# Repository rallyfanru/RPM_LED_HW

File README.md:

# RPM_LED_HW
Аппаратная часть проекта https://github.com/rallyfanru/RPM_LED  
Проект сделан в Kicad 5  
Требует исправления, список ошибок в changelog.txt

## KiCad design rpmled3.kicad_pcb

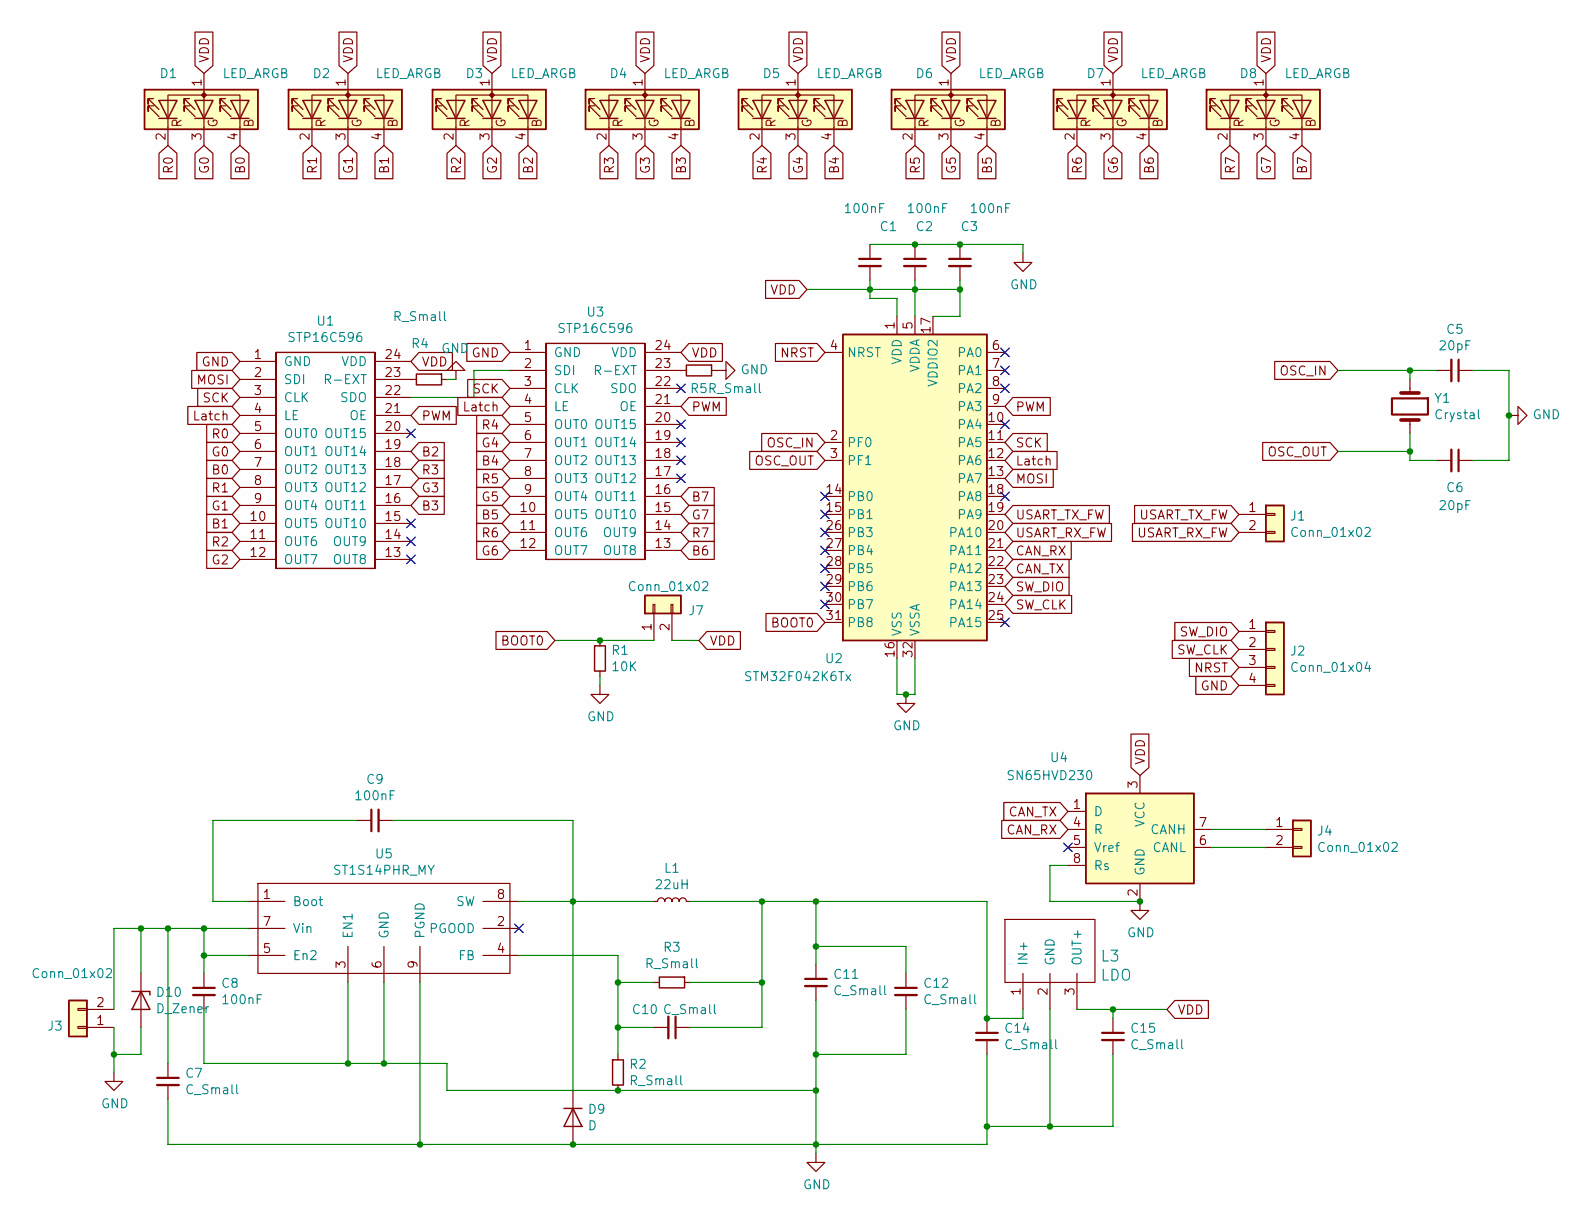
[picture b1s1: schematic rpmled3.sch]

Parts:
C1, C2, C3, C8, C9: 100nF; C_0805_2012Metric_Pad1.15x1.40mm_HandSolder
C5, C6: 20pF; C_0805_2012Metric_Pad1.15x1.40mm_HandSolder
C7, C14, C15: C_Small; C_1206_3216Metric_Pad1.42x1.75mm_HandSolder
C10: C_Small; C_0805_2012Metric_Pad1.15x1.40mm_HandSolder
C11, C12: C_Small; CP_EIA-7343-31_Kemet-D_Pad2.25x2.55mm_HandSolder
D1, D2, D3, D4, D5, D6, D7, D8: LED_ARGB; RGB_LEB_InLine
D9: D; D_SMB_Handsoldering
D10: D_Zener; D_DO-201AD_P12.70mm_Horizontal
J1, J3, J4, J7: Conn_01x02; PinHeader_1x02_P2.54mm_Vertical
J2: Conn_01x04; PinHeader_1x04_P2.54mm_Vertical
L1: 22uH; L_10.4x10.4_H4.8
L3: LDO; TO-252-3_TabPin2
R1: 10K; R_1206_3216Metric_Pad1.42x1.75mm_HandSolder
R2, R3: R_Small; R_0603_1608Metric_Pad1.05x0.95mm_HandSolder
R4, R5: R_Small; R_1206_HandSoldering
U1, U3: STP16C596; SOIC-24W_7.5x15.4mm_P1.27mm
U2: STM32F042K6Tx; LQFP-32_7x7mm_P0.8mm
U4: SN65HVD230; SOIC-8_3.9x4.9mm_P1.27mm
U5: ST1S14PHR_MY; SOIC-8-1EP_3.9x4.9mm_P1.27mm_EP2.35x2.35mm
Y1: Crystal; Crystal_HC49-4H_Vertical

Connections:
B0: D1.4 (BK), U1.7 (OUT2)
B1: D2.4 (BK), U1.10 (OUT5)
B2: D3.4 (BK), U1.19 (OUT14)
B3: D4.4 (BK), U1.16 (OUT11)
B4: D5.4 (BK), U3.7 (OUT2)
B5: D6.4 (BK), U3.10 (OUT5)
B6: D7.4 (BK), U3.13 (OUT8)
B7: D8.4 (BK), U3.16 (OUT11)
BOOT0: J7.1, R1.1, U2.31 (PB8)
CAN_RX: U2.21 (PA11), U4.4 (R)
CAN_TX: U2.22 (PA12), U4.1 (D)
G0: D1.3 (GK), U1.6 (OUT1)
G1: D2.3 (GK), U1.9 (OUT4)
G2: D3.3 (GK), U1.12 (OUT7)
G3: D4.3 (GK), U1.17 (OUT12)
G4: D5.3 (GK), U3.6 (OUT1)
G5: D6.3 (GK), U3.9 (OUT4)
G6: D7.3 (GK), U3.12 (OUT7)
G7: D8.3 (GK), U3.15 (OUT10)
GND: C1.1, C2.1, C3.1, C5.1, C6.1, C7.2, C8.2, C11.2, C12.2, C14.2, C15.2, D9.2 (A), D10.2 (A), J2.4, J3.1, L3.2 (GND), R1.2, R2.2, R4.1, R5.1, U1.1 (GND), U2.16 (VSS), U2.32 (VSSA), U3.1 (GND), U4.2 (GND), U4.8 (Rs), U5.3 (EN1), U5.6 (GND), U5.9 (PGND)
Latch: U1.4 (LE), U2.12 (PA6), U3.4 (LE)
MOSI: U1.2 (SDI), U2.13 (PA7)
NRST: J2.3, U2.4 (NRST)
unnamed: C7.1, C8.1, D10.1 (K), J3.2, U5.5 (En2), U5.7 (Vin)
unnamed: C9.1, U5.1 (Boot)
unnamed: C9.2, D9.1 (K), L1.1, U5.8 (SW)
unnamed: C10.1, C11.1, C12.1, C14.1, L1.2, L3.1 (IN+), R3.1
unnamed: C10.2, R2.1, R3.2, U5.4 (FB)
unnamed: J4.1, U4.7 (CANH)
unnamed: J4.2, U4.6 (CANL)
unnamed: R4.2, U1.23 (R-EXT)
unnamed: R5.2, U3.23 (R-EXT)
unnamed: U1.22 (SDO), U3.2 (SDI)
OSC_IN: C5.2, U2.2 (PF0), Y1.1
OSC_OUT: C6.2, U2.3 (PF1), Y1.2
PWM: U1.21 (OE), U2.9 (PA3), U3.21 (OE)
R0: D1.2 (RK), U1.5 (OUT0)
R1: D2.2 (RK), U1.8 (OUT3)
R2: D3.2 (RK), U1.11 (OUT6)
R3: D4.2 (RK), U1.18 (OUT13)
R4: D5.2 (RK), U3.5 (OUT0)
R5: D6.2 (RK), U3.8 (OUT3)
R6: D7.2 (RK), U3.11 (OUT6)
R7: D8.2 (RK), U3.14 (OUT9)
SCK: U1.3 (CLK), U2.11 (PA5), U3.3 (CLK)
SW_CLK: J2.2, U2.24 (PA14)
SW_DIO: J2.1, U2.23 (PA13)
USART_RX_FW: J1.2, U2.20 (PA10)
USART_TX_FW: J1.1, U2.19 (PA9)
VDD: C1.2, C2.2, C3.2, C15.1, D1.1 (A), D2.1 (A), D3.1 (A), D4.1 (A), D5.1 (A), D6.1 (A), D7.1 (A), D8.1 (A), J7.2, L3.3 (OUT+), U1.24 (VDD), U2.1 (VDD), U2.5 (VDDA), U2.17 (VDDIO2), U3.24 (VDD), U4.3 (VCC)

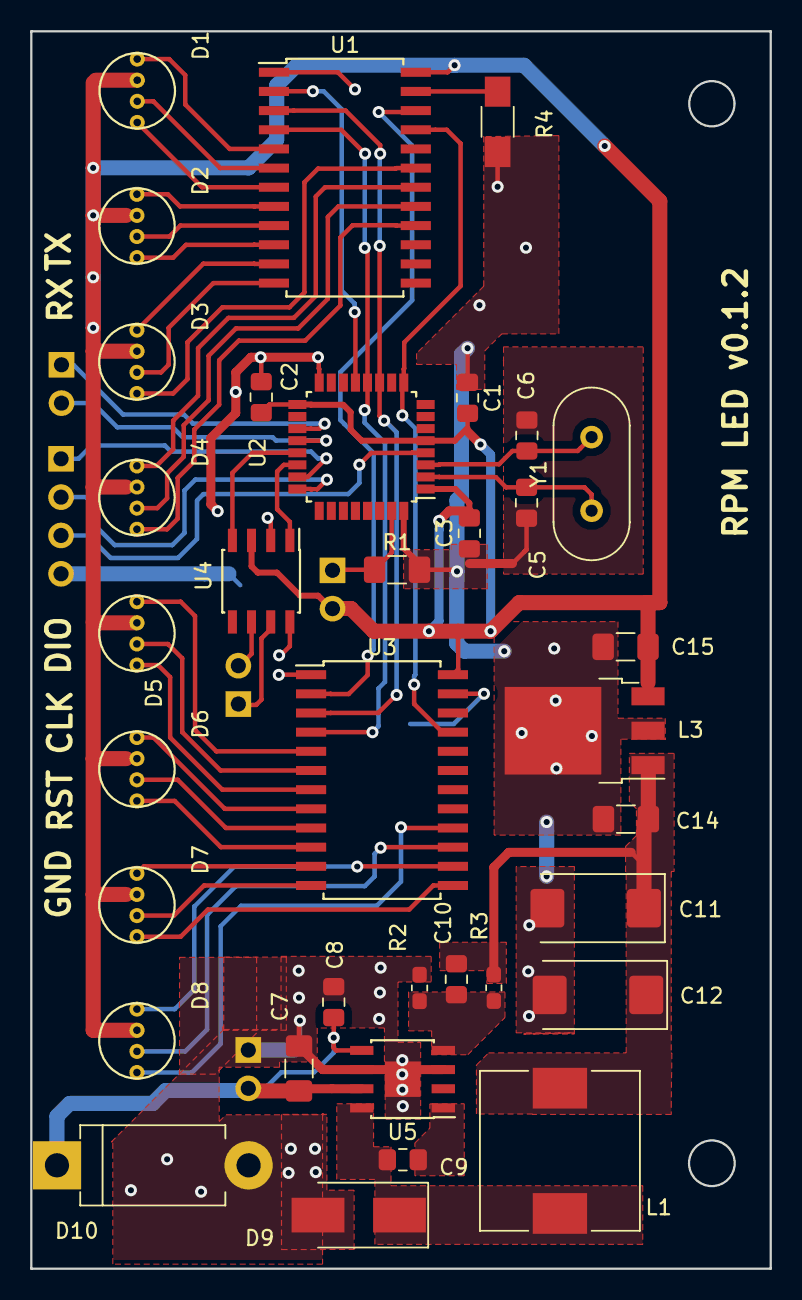
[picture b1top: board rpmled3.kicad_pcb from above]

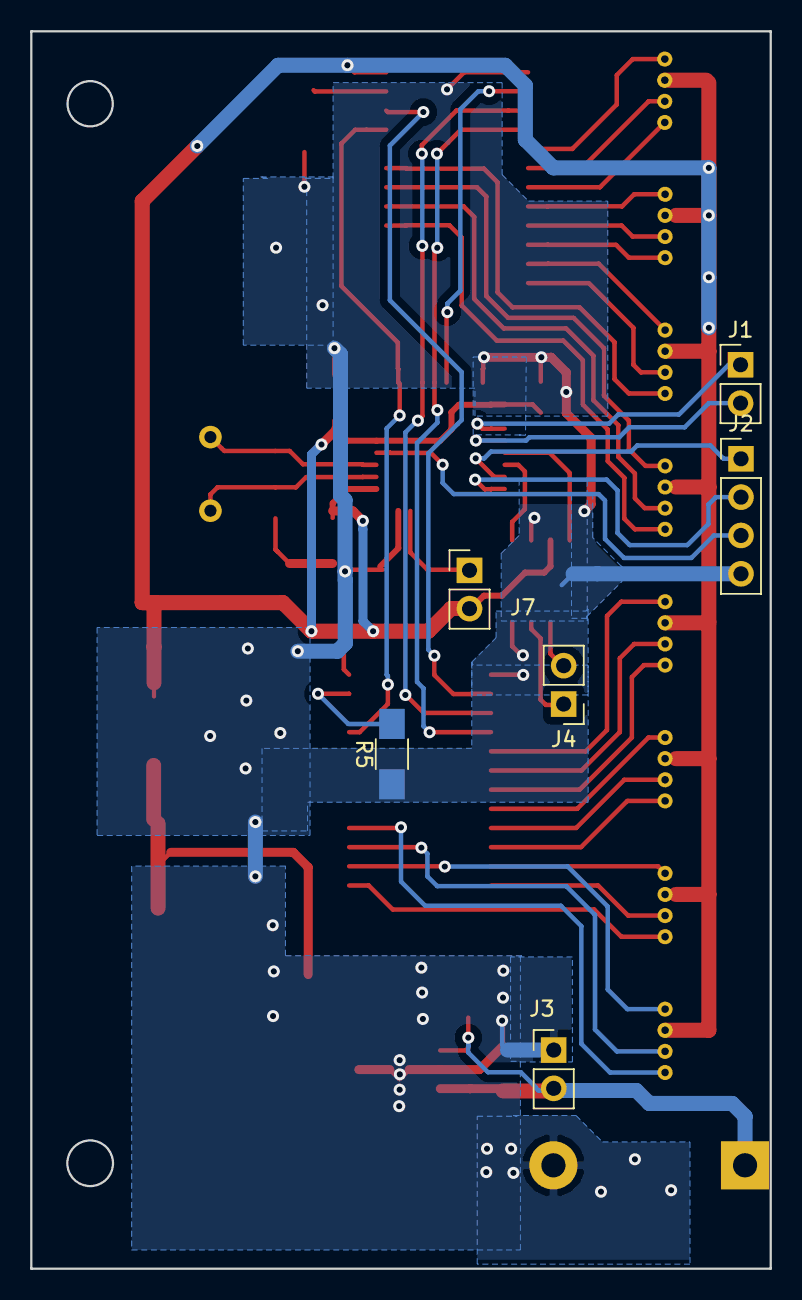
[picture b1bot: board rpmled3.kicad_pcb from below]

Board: 2 copper layers, 49.0 x 82.0 mm, 41 parts (6 on the bottom side), 50 nets.

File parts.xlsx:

|  |  |  |  |  | Итого: | 753.31
 | Обозначение | Элемент | Номинал | Корпус | Код | Ссылка | Цена
 | C11 | конденсатор | 100u | SMD D | 593D107X9010D2TE3 | https://spb.terraelectronica.ru/product/358908 | 24.6
 | C12 | конденсатор | 100u | SMD D | 593D107X9010D2TE3 | https://spb.terraelectronica.ru/product/358908 | 24.6
 | C10 | конденсатор | 1.5p | 0805 | CC0805CRNPO9BN1R5 | https://spb.terraelectronica.ru/product/1107359 | 1.3
 | C5 | конденсатор | 20p | 0805 | CC0805JRNPO9BN200 | https://spb.terraelectronica.ru/product/326950 | 1.3
 | C6 | конденсатор | 20p | 0805 | CC0805JRNPO9BN200 | https://spb.terraelectronica.ru/product/326950 | 1.3
 | C1 | конденсатор | 100n | 0805 | CC0805ZRY5V9BB104 | https://spb.terraelectronica.ru/product/360375 | 2.2
 | C2 | конденсатор | 100n | 0805 | CC0805ZRY5V9BB104 | https://spb.terraelectronica.ru/product/360375 | 2.2
 | C3 | конденсатор | 100n | 0805 | CC0805ZRY5V9BB104 | https://spb.terraelectronica.ru/product/360375 | 2.2
 | C8 | конденсатор | 100n | 0805 | CC0805ZRY5V9BB104 | https://spb.terraelectronica.ru/product/360375 | 2.2
 | C9 | конденсатор | 100n | 0805 | CC0805ZRY5V9BB104 | https://spb.terraelectronica.ru/product/360375 | 2.2
 | C7 | конденсатор | 4.7u | 1206 | CC1206KKX7R9BB475 | https://spb.terraelectronica.ru/product/1320438 | 29.2
 | C14 | конденсатор | 10u | 1206 | CL31B106KPHNNNE | https://spb.terraelectronica.ru/product/1641462 | 6.1
 | C15 | конденсатор | 4.7u | 1206 | GRM31CR71A475KA01L | https://spb.terraelectronica.ru/product/361734 | 8.7
 | D10 | сапрессор | 18B |  | 1.5KE18CA | https://www.chipdip.ru/product/1.5ke18ca | 16
 | D9 | Диод |  | SMB | STPS2L25U | https://spb.terraelectronica.ru/product/236375 | 8.8
 | L1 | индуктивность |  |  | IHLP2525CZER8R2M01 | https://spb.terraelectronica.ru/product/577217 | 36.9
 | L3 | LDO |  |  | NCP5501DT33RKG | https://spb.terraelectronica.ru/product/437019 | 24.8
 | R1 | резистор | 10K | 1206 | CR1206-JW-103ELF | https://spb.terraelectronica.ru/product/1628762 | 0.5
 | R2 | резистор | 60.4K | 0603 | RC0603FR-0760K4L | https://spb.terraelectronica.ru/product/871175 | 0.15
 | R3 | резистор | 187K | 0603 | RC0603FR-07187KL | https://spb.terraelectronica.ru/product/871017 | 0.42
 | R4 | резистор | 1K | 1206 | CR1206-JW-102ELF | https://spb.terraelectronica.ru/product/265324 | 0.62
 | R5 | резистор | 1K | 1206 | CR1206-JW-102ELF | https://spb.terraelectronica.ru/product/265324 | 0.62
 | U1 | STP16CP05 |  |  | STP16CP05MTR | https://spb.terraelectronica.ru/product/274946 | 71.5
 | U2 | STM32F042 |  |  | STM32F042K6T6 | https://spb.terraelectronica.ru/product/1334269 | 160
 | U3 | STP16CP05 |  |  | STP16CP05MTR | https://spb.terraelectronica.ru/product/274946 | 71.5
 | U4 | CAN |  |  | SN65HVD230 | https://spb.terraelectronica.ru/product/176199 | 145
 | U5 | dc-dc |  |  | ST1S14PHR | https://spb.terraelectronica.ru/product/674771 | 96
 | Y1 | Кварц |  |  | KX-3H 8.0 MHz | https://spb.terraelectronica.ru/product/31625 | 12.4

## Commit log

2018-12-20 Начальный коммит Версия 0.1, есть ошибки.
2018-12-20 Список ошибок
2018-12-20 Не стандартные компоненты перенесены в локальную библиотеку Исправления v0.1.2
